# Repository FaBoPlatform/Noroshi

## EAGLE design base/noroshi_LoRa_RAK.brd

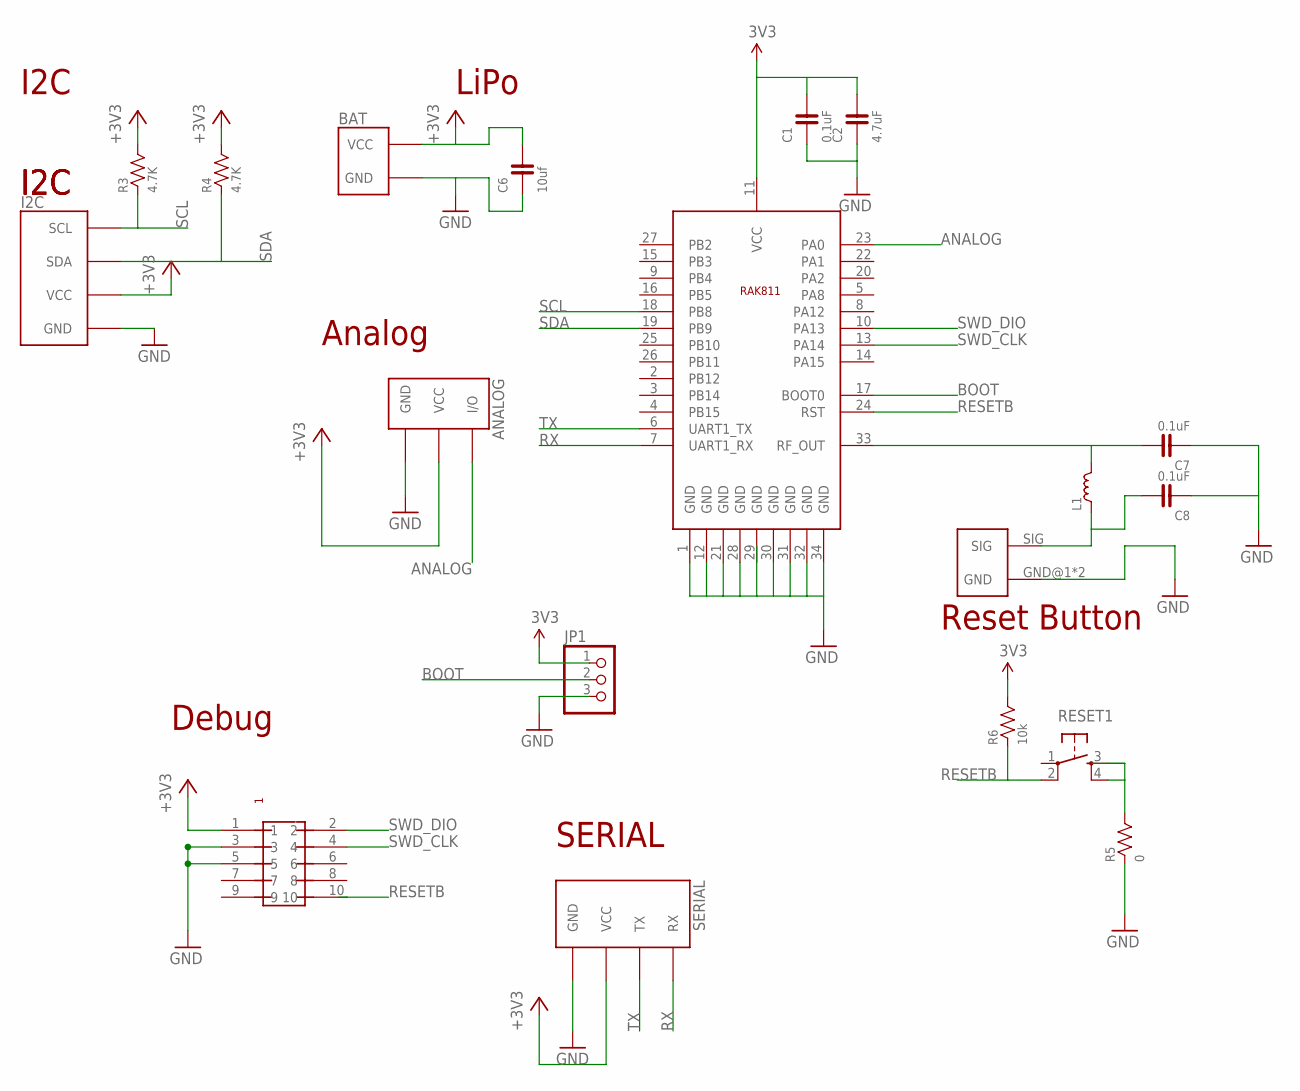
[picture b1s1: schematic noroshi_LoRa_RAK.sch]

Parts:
ANALOG: FABO_BRICK_3PIN-S03B-PASK-2_LONG; FABO_BRICK_3PIN_S03B-PASK-2_LONG
BAT: FABO_BRICK_2PIN_SIDE; FABO_BRICK_2PIN_S02B−PASK-2_SILK
C1, C7, C8: 0.1uF; 0603-NARROW
C2: 4.7uF; 0603-NARROW
C6: 10uf; 0603
I2C: FABO_BRICK_I2C-S04B-PASK-2_LONG; FABO_BRICK_I2C_S04B-PASK-2_LONG
JP1: PINHD-1X3; 1X03
L1: COIL-0603; 0603
R3, R4: 4.7K; 0603
R5: 0; 0603-NARROW
R6: 10k; 0603-NARROW
RESET1: TACT-SWITCH-SMD_KMR2; KMR2
SERIAL: FABO_BRICK_SERIAL-S04B-PASK-2_LONG; FABO_BRICK_SERIAL_S04B-PASK-2_LONG
U$2: RAK811
U$8: PIN-HEADER-SMT(1.27MM)2X5
UF1: HIROSE-U.FL; HIROSE-UF.L

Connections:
3V3: C1.2, C2.2, JP1.1, R6.2, U$2.11 (VCC)
+3V3: ANALOG.VCC, BAT.VCC, C6.2, I2C.VCC, R3.2, R4.2, SERIAL.VCC, U$8.1
ANALOG: ANALOG.I/O, U$2.23 (PA0)
BOOT: JP1.2, U$2.17 (BOOT0)
GND: ANALOG.GND, BAT.GND, C1.1, C2.1, C6.1, C7.1, C8.1, I2C.GND, JP1.3, R5.1, SERIAL.GND, U$2.1 (GND), U$2.12 (GND), U$2.21 (GND), U$2.28 (GND), U$2.30 (GND), U$2.31 (GND), U$2.32 (GND), U$2.34 (GND), U$8.3, U$8.5, UF1.GND@1 (GND), UF1.GND@2 (GND)
unnamed: C7.2, L1.2, U$2.33 (RF_OUT)
unnamed: C8.2, L1.1, UF1.SIG
unnamed: R5.2, RESET1.3, RESET1.4
RESETB: R6.1, RESET1.2, U$2.24 (RST), U$8.10
RX: SERIAL.RX, U$2.7 (UART1_RX)
SCL: I2C.SCL, R3.1, U$2.18 (PB8)
SDA: I2C.SDA, R4.1, U$2.19 (PB9)
SWD_CLK: U$2.13 (PA14), U$8.4
SWD_DIO: U$2.10 (PA13), U$8.2
TX: SERIAL.TX, U$2.6 (UART1_TX)

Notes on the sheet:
I2C
SERIAL
LiPo
Reset Button
Debug
Analog

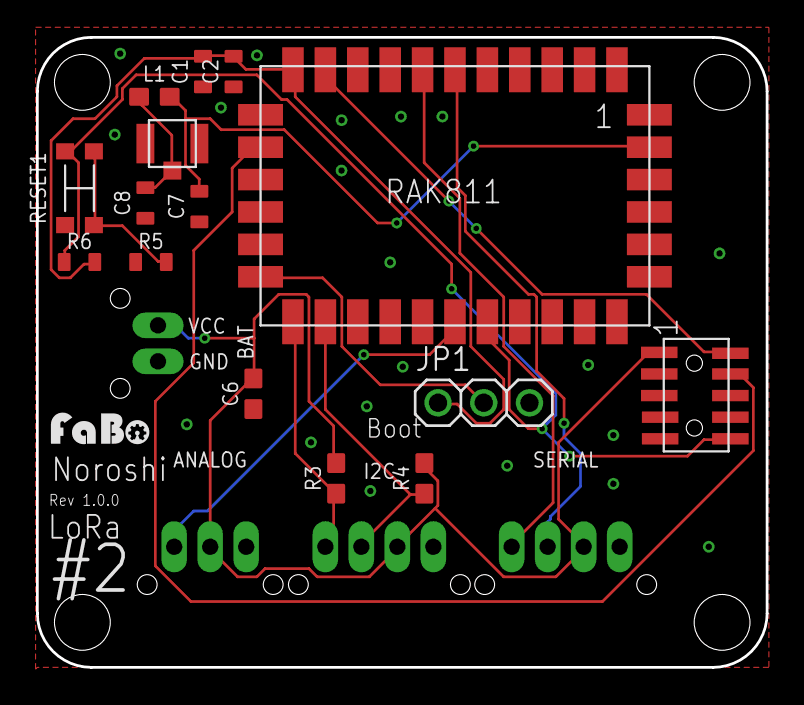
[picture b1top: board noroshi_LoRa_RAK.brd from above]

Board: 2 copper layers, 40.5 x 35.0 mm, 21 parts (0 on the bottom side), 15 nets.

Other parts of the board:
U$1: FABO-SHINOBI
U$3: LOGO_FABO_S

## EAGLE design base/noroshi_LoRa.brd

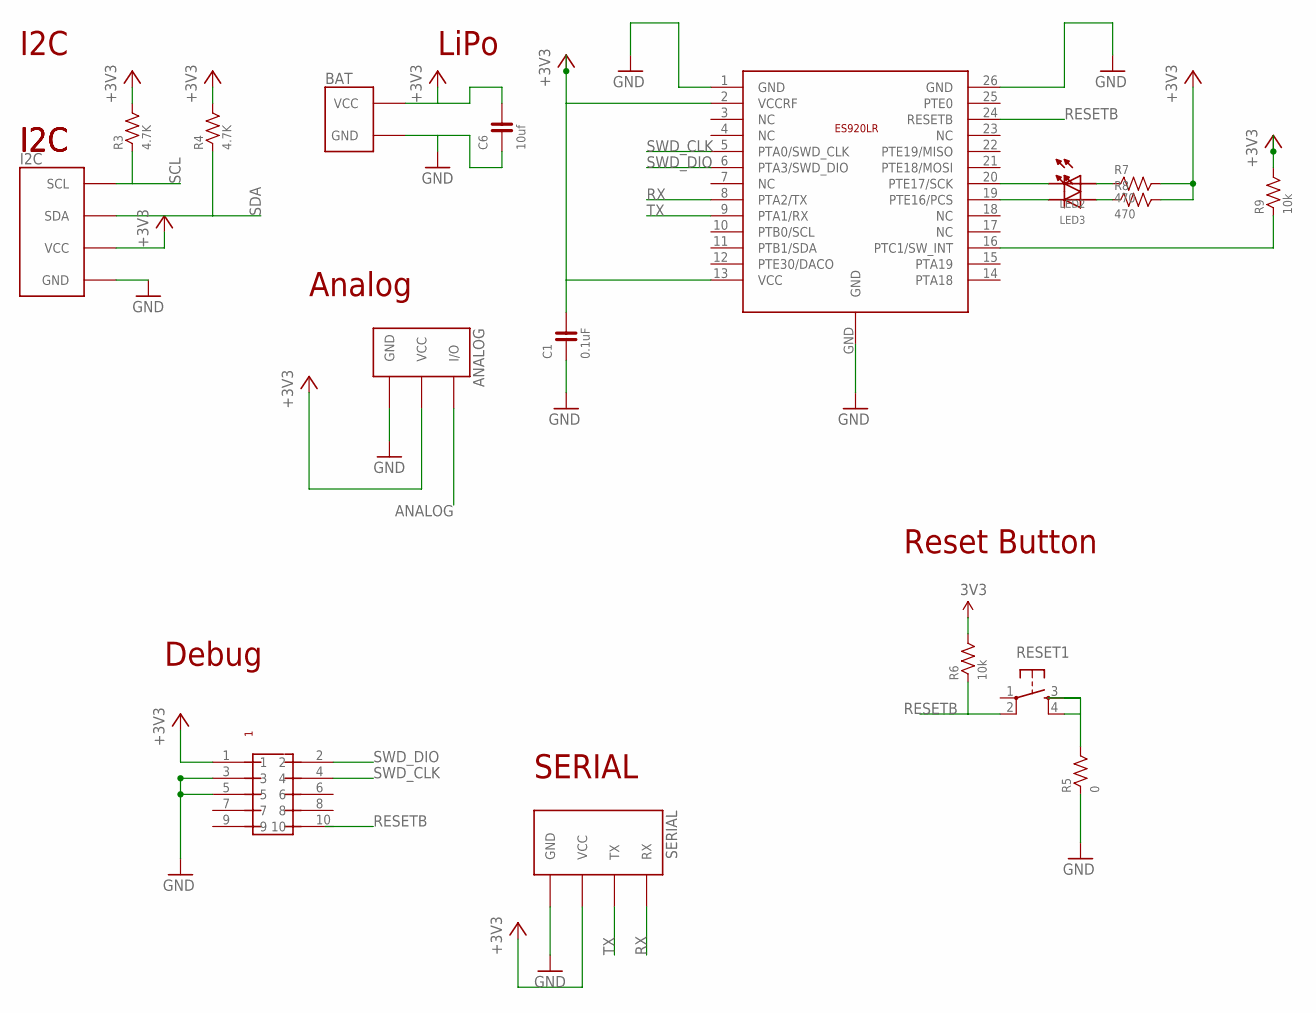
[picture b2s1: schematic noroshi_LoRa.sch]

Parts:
ANALOG: FABO_BRICK_3PIN-S03B-PASK-2_LONG; FABO_BRICK_3PIN_S03B-PASK-2_LONG
BAT: FABO_BRICK_2PIN_SIDE; FABO_BRICK_2PIN_S02B−PASK-2_SILK
C1: 0.1uF; 0603-NARROW
C6: 10uf; 0603
I2C: FABO_BRICK_I2C-S04B-PASK-2_LONG; FABO_BRICK_I2C_S04B-PASK-2_LONG
LED2, LED3: LED-0603; 0603
R3, R4: 4.7K; 0603
R5: 0; 0603-NARROW
R6, R9: 10k; 0603-NARROW
R7, R8: 470; 0603-NARROW
RESET1: TACT-SWITCH-SMD_KMR2; KMR2
SERIAL: FABO_BRICK_SERIAL-S04B-PASK-2_LONG; FABO_BRICK_SERIAL_S04B-PASK-2_LONG
U$2: ES920LR
U$8: PIN-HEADER-SMT(1.27MM)2X5

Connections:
3V3: R6.2
+3V3: ANALOG.VCC, BAT.VCC, C1.2, C6.2, I2C.VCC, R3.2, R4.2, R7.2, R8.2, R9.2, SERIAL.VCC, U$2.2 (VCCRF), U$2.13 (VCC), U$8.1
ANALOG: ANALOG.I/O
GND: ANALOG.GND, BAT.GND, C1.1, C6.1, I2C.GND, R5.1, SERIAL.GND, U$2.1 (GND), U$2.26 (GND), U$2.GND, U$8.3, U$8.5
unnamed: LED3.CATHODE, U$2.19 (PTE16/PCS)
unnamed: LED2.CATHODE, U$2.20 (PTE17/SCK)
unnamed: LED2.ANODE, R7.1
unnamed: LED3.ANODE, R8.1
unnamed: R9.1, U$2.16 (PTC1/SW_INT)
unnamed: R5.2, RESET1.3, RESET1.4
RESETB: R6.1, RESET1.2, U$2.24 (RESETB), U$8.10
RX: SERIAL.RX, U$2.8 (PTA2/TX)
SCL: I2C.SCL, R3.1
SDA: I2C.SDA, R4.1
SWD_CLK: U$2.5 (PTA0/SWD_CLK), U$8.4
SWD_DIO: U$2.6 (PTA3/SWD_DIO), U$8.2
TX: SERIAL.TX, U$2.9 (PTA1/RX)

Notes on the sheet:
I2C
SERIAL
LiPo
Reset Button
Debug
Analog

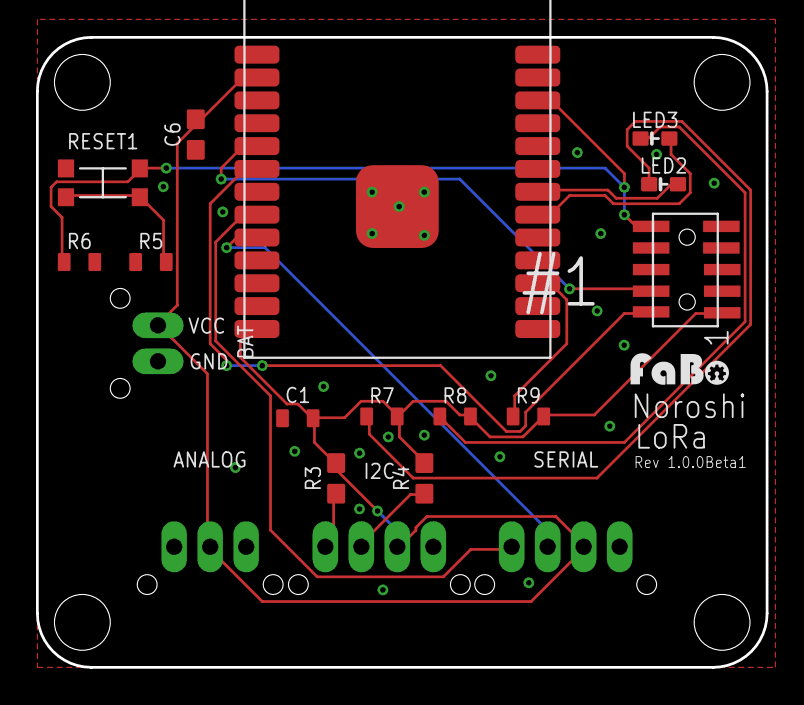
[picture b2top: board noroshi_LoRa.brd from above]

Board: 2 copper layers, 40.5 x 35.0 mm, 20 parts (0 on the bottom side), 15 nets.

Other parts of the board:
U$1: FABO-SHINOBI
U$3: LOGO_FABO_S

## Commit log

2017-12-25 Initial commit.
2018-03-22 Update noroshi.

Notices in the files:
parts and their libraries:
FaBo-LED: Released under the Creative Commons Attribution-ShareAlike 4.0 License
https://creativecommons.org/licenses/by-sa/4.0
gclue: Released under the Creative Commons
